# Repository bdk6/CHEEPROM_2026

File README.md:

# CHEEPROM_2026
Programmer for AT28C64 and AT28C256 EEPROM chips

This is a simple programmer based on an Arduino Nano (ATMega328) module or compatible.  
In addition to the Nano it has two 74hc595 shift registers, a couple of LEDs and resistors, and a 
Zero Insertion Force (ZIF) socket for the EEPROM.

There is a special PC program written in C to run on Linux for controlling the programmer.  I 
try to avoid Windows as much as possible, so if you want to go that route you're on your 
own.

Currently, the only one I have built is on a prototyping board.  I may or may not lay out a 
PCB for the current version.  I am planning to build a much more capable version in the near 
future that will also be able to handle Intel type 27xxx Eproms and perhaps some other chips 
so I may not bother with a PCB for this one.

In this repo are the schematic and parts list, the Arduino code, and the Linux C code.  The 
Arduino code was written and tested using Arduino IDE 1.8.19.  Other versions might cause 
problems.

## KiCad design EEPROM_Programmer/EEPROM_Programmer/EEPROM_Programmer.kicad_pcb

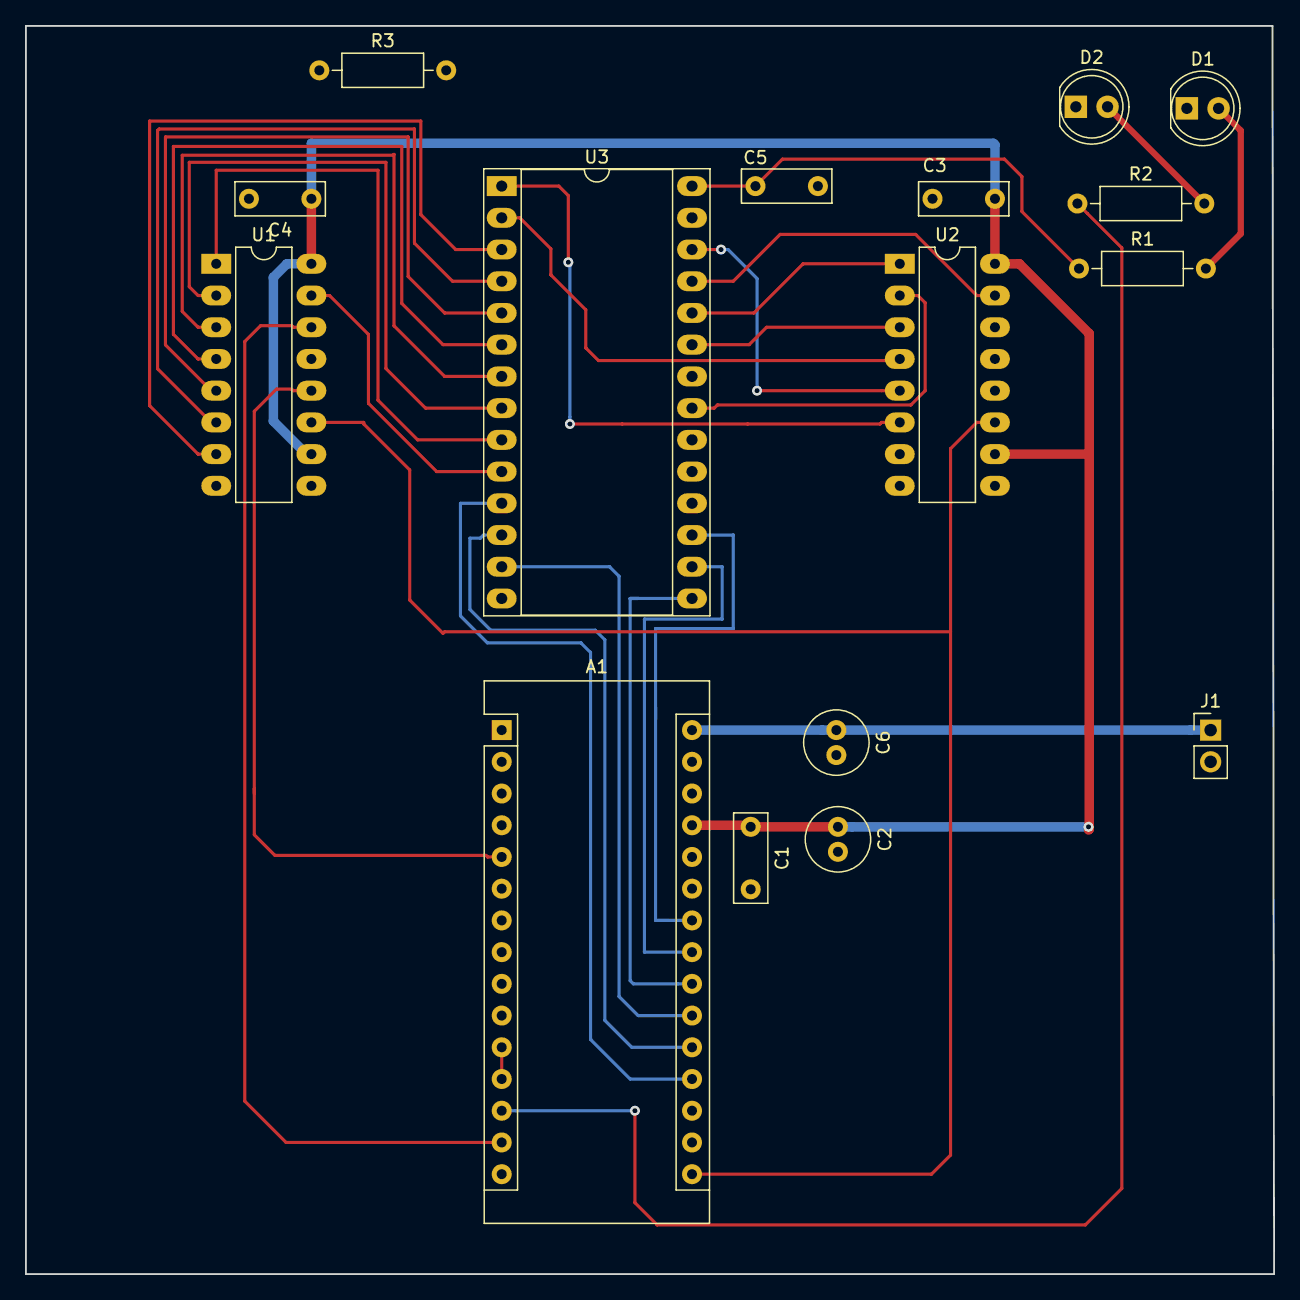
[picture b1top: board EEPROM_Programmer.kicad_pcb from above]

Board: 2 copper layers, 99.9 x 99.9 mm, 16 parts (0 on the bottom side), 38 nets.

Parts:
A1: Arduino_Nano_v3.x; Arduino_Nano
C1, C3, C4: 0.1; C_Rect_L7.0mm_W2.5mm_P5.00mm
C2, C6: 10; C_Radial_D5.0mm_H11.0mm_P2.00mm
C5: 1.0; C_Rect_L7.0mm_W2.5mm_P5.00mm
D1: Red; LED_D5.0mm
D2: Green; LED_D5.0mm
J1: Vin; PinHeader_1x02_P2.54mm_Vertical
R1, R2: 470; R_Axial_DIN0207_L6.3mm_D2.5mm_P10.16mm_Horizontal
R3: 4K7; R_Axial_DIN0207_L6.3mm_D2.5mm_P10.16mm_Horizontal
U1, U2: 74HC595; DIP-16_W7.62mm_LongPads
U3: 28C256; ZIF_3M_28_DIP-28_W15.24mm_Socket_LongPads

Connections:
GND: A1.4, A1.29, C1.2, C2.2, C3.2, C4.2, C5.2, C6.2, D1.1, D2.1, J1.2, U1.8, U1.13, U2.8, U2.13, U3.14
unnamed: A1.5, U1.12, U2.12
unnamed: A1.6, U3.20
unnamed: A1.7, U3.22
unnamed: A1.8, U3.27
unnamed: A1.9, U3.18
unnamed: A1.10, U3.19
unnamed: A1.11, A1.12, C5.1, R1.1, U3.28
unnamed: A1.13, R2.1
unnamed: A1.14, U1.14
unnamed: A1.16, U1.11, U2.11
unnamed: A1.19, U3.11
unnamed: A1.20, U3.12
unnamed: A1.21, U3.13
unnamed: A1.22, U3.15
unnamed: A1.23, U3.16
unnamed: A1.24, U3.17
unnamed: A1.30, C6.1, J1.1
unnamed: D1.2, R1.2
unnamed: D2.2, R2.2
unnamed: R3.1, U3.1
unnamed: R3.2, U2.6
unnamed: U1.1, U3.9
unnamed: U1.2, U3.8
unnamed: U1.3, U3.7
unnamed: U1.4, U3.6
unnamed: U1.5, U3.5
unnamed: U1.6, U3.4
unnamed: U1.7, U3.3
unnamed: U1.9, U2.14
unnamed: U1.15, U3.10
unnamed: U2.1, U3.24
unnamed: U2.2, U3.21
unnamed: U2.3, U3.23
unnamed: U2.4, U3.2
unnamed: U2.5, U3.26
unnamed: U2.15, U3.25
VCC: A1.27, C1.1, C2.1, C3.1, C4.1, U1.10, U1.16, U2.10, U2.16

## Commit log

2026-05-24 CHEEPROM_2026 First version of working code
2026-05-25 CHEEPROM_2026 Added FILL command and did cleanup.
2026-05-26 CHEEPROM_2026 Cleaned up PC program.
2026-05-26 CHEEPROM_2026 More cleanup of PC code.
2026-06-12 Added design files.
2026-06-12 Added EEPROM_Programmer project as backup.
